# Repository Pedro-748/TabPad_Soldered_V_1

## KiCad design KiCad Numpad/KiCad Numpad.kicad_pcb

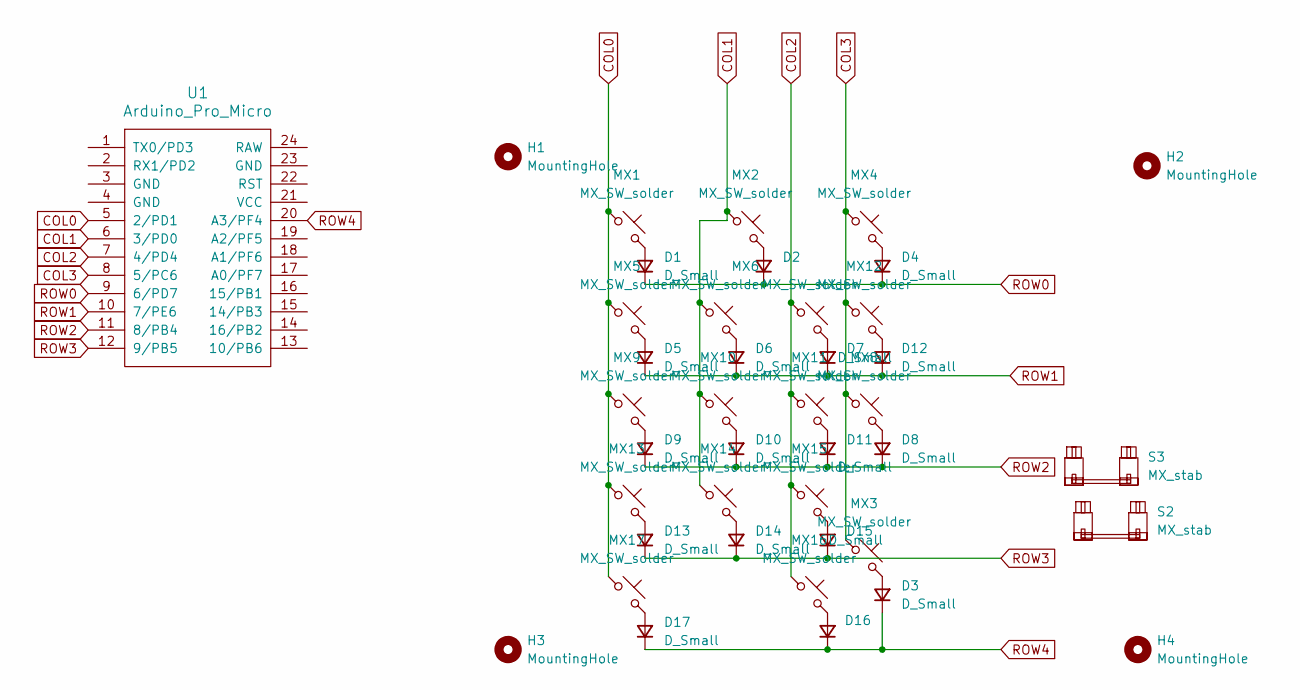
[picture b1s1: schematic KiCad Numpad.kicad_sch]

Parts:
D1, D2, D3, D4, D5, D6, D7, D8, D9, D10, D11, D12, D13, D14, D15, D16, D17: D_Small; D_SOD-123
H1, H2, H3, H4: MountingHole; MountingHole_2.2mm_M2
MX1, MX3, MX5, MX6, MX7, MX8, MX9, MX10, MX11, MX12, MX13, MX14, MX15, MX16, MX17: MX_SW_solder; SW_MX_1u
MX2, MX4: MX_SW_solder; SW_MX_1.5u
S2, S3: MX_stab; STAB_MX_2u
U1: Arduino_Pro_Micro

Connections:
COL0: MX1.1, MX5.1, MX9.1, MX13.1, MX17.1, U1.5 (2/PD1)
COL1: MX2.1, MX6.1, MX10.1, MX14.1, U1.6 (3/PD0)
COL2: MX7.1, MX11.1, MX15.1, MX16.1, U1.7 (4/PD4)
COL3: MX3.1, MX4.1, MX8.1, MX12.1, U1.8 (5/PC6)
unnamed: D1.2 (A), MX1.2
unnamed: D2.2 (A), MX2.2
unnamed: D3.2 (A), MX3.2
unnamed: D4.2 (A), MX4.2
unnamed: D5.2 (A), MX5.2
unnamed: D6.2 (A), MX6.2
unnamed: D7.2 (A), MX7.2
unnamed: D8.2 (A), MX8.2
unnamed: D9.2 (A), MX9.2
unnamed: D10.2 (A), MX10.2
unnamed: D11.2 (A), MX11.2
unnamed: D12.2 (A), MX12.2
unnamed: D13.2 (A), MX13.2
unnamed: D14.2 (A), MX14.2
unnamed: D15.2 (A), MX15.2
unnamed: D16.2 (A), MX16.2
unnamed: D17.2 (A), MX17.2
ROW0: D1.1 (K), D2.1 (K), D4.1 (K), U1.9 (6/PD7)
ROW1: D5.1 (K), D6.1 (K), D7.1 (K), D12.1 (K), U1.10 (7/PE6)
ROW2: D8.1 (K), D9.1 (K), D10.1 (K), D11.1 (K), U1.11 (8/PB4)
ROW3: D13.1 (K), D14.1 (K), D15.1 (K), U1.12 (9/PB5)
ROW4: D3.1 (K), D16.1 (K), D17.1 (K), U1.20 (A3/PF4)

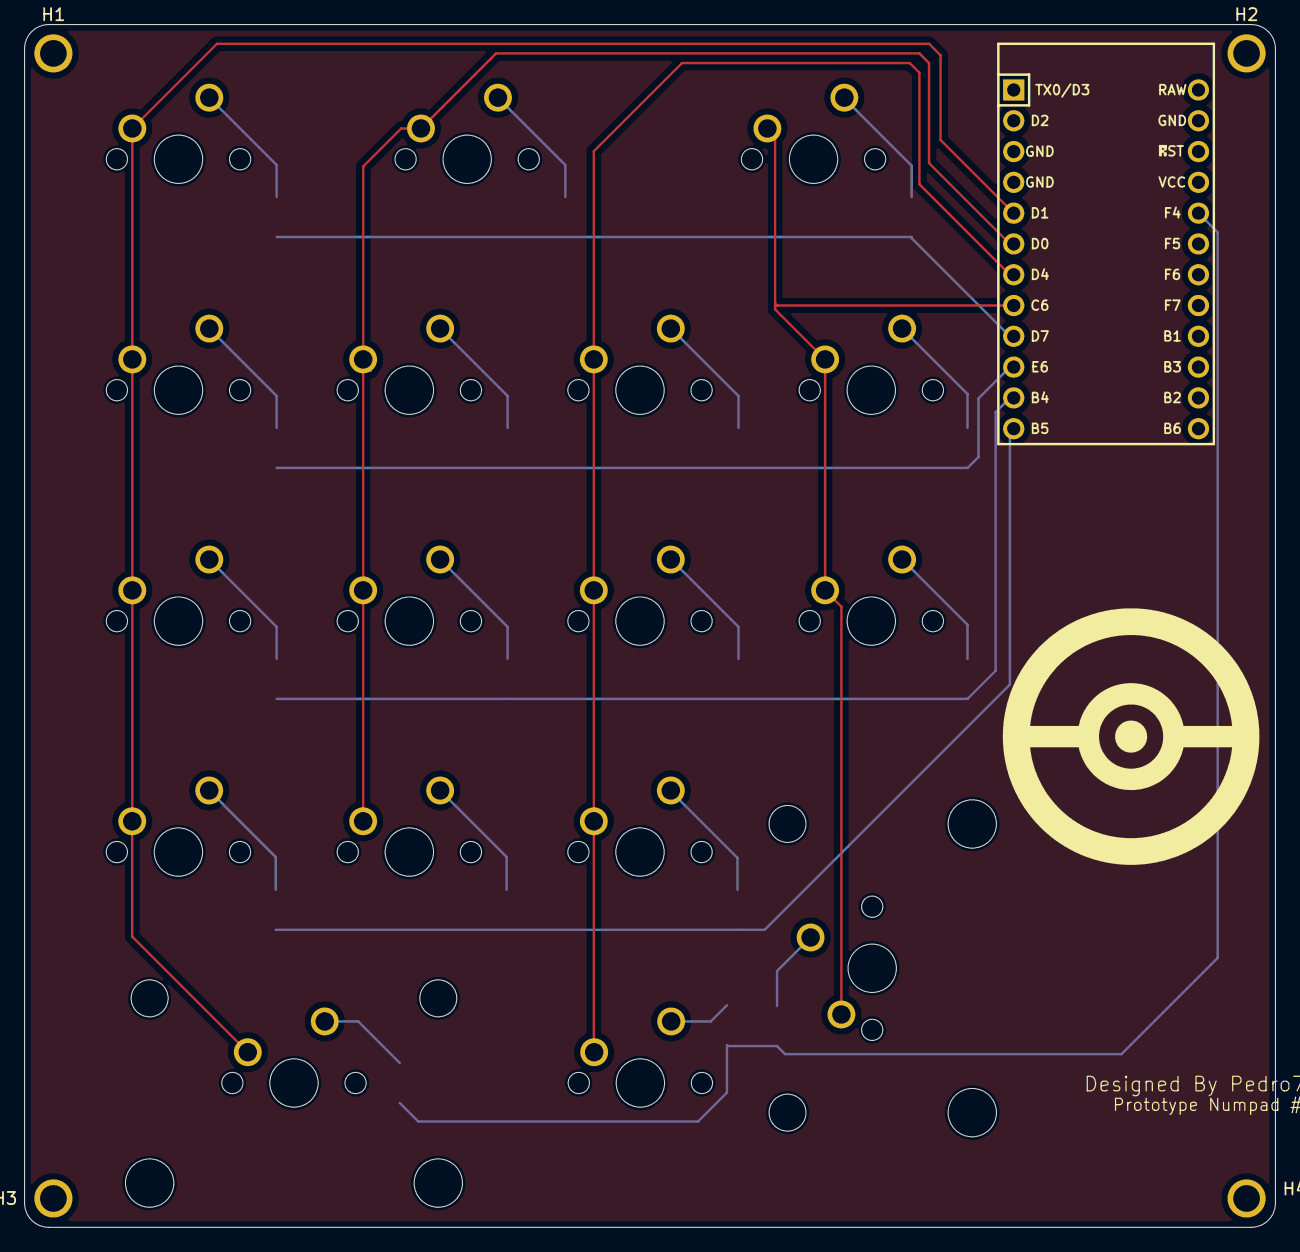
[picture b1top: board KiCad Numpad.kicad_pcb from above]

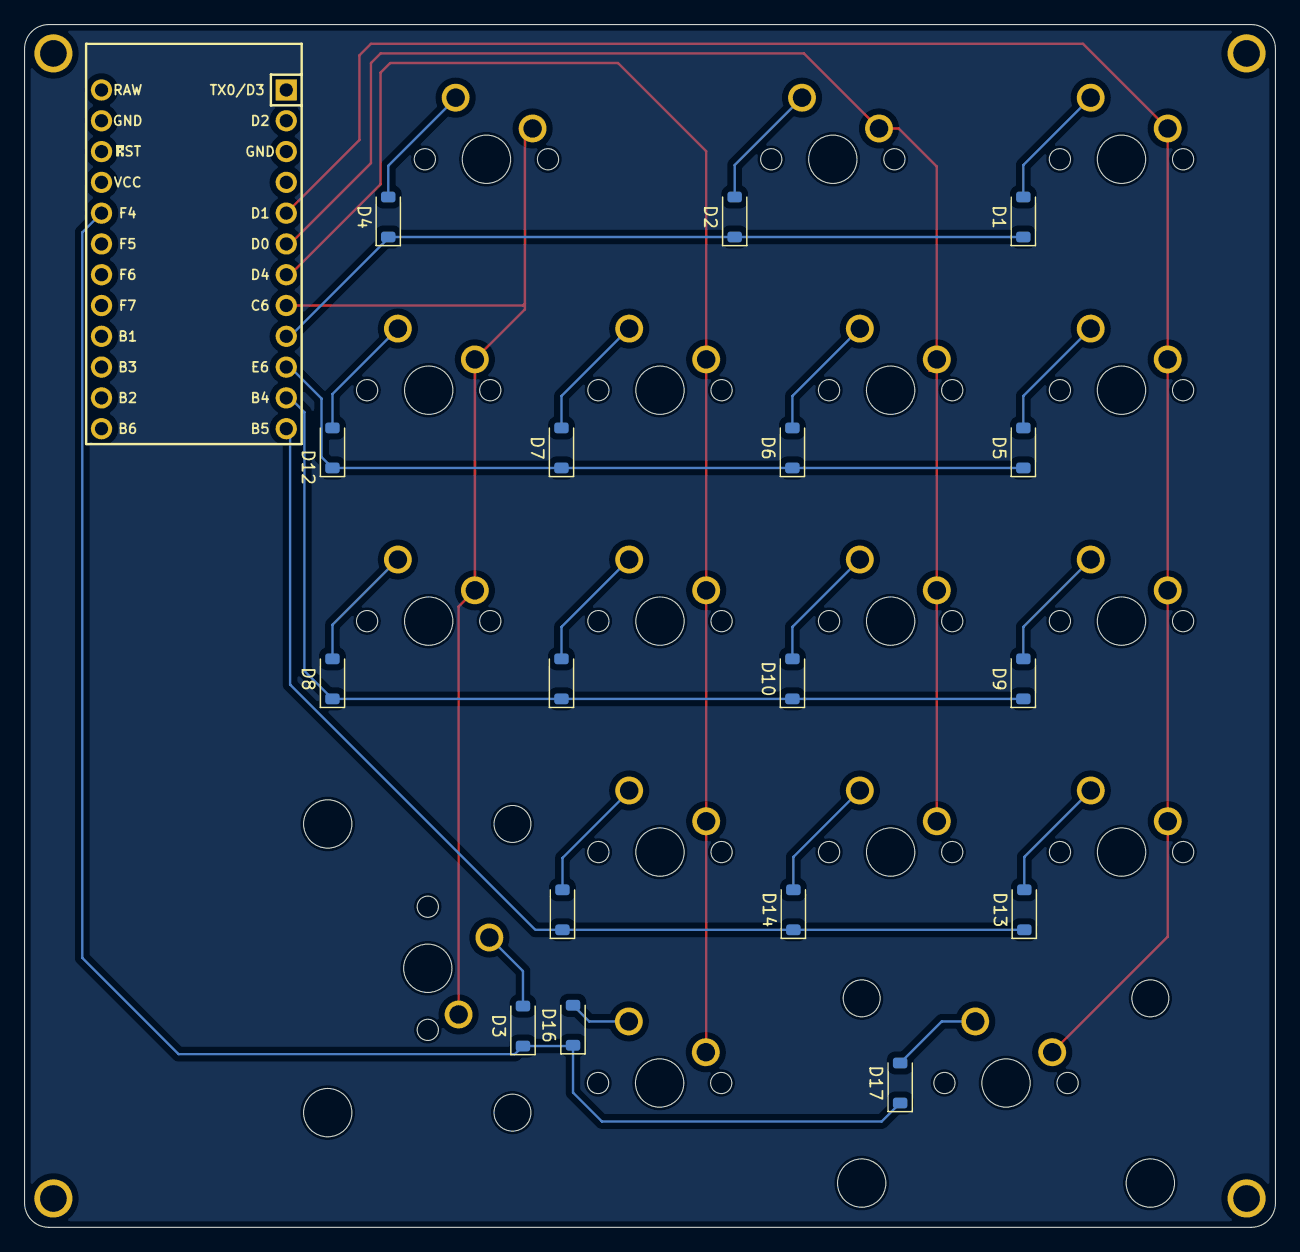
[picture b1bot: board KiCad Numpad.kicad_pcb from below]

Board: 2 copper layers, 103.2 x 99.2 mm, 41 parts (17 on the bottom side), 26 nets.

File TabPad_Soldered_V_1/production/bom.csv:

Designator,Footprint,Quantity,Value,LCSC Part #
"D1, D10, D11, D12, D13, D14, D15, D16, D17, D2, D3, D4, D5, D6, D7, D8, D9",D_SOD-123,17,D_Small,
"MX1, MX10, MX11, MX12, MX13, MX14, MX15, MX16, MX17, MX3, MX5, MX6, MX7, MX8, MX9",SW_MX_1u,15,MX_SW_solder,
"MX2, MX4",SW_MX_1.5u,2,MX_SW_solder,
"S2, S3",STAB_MX_2u,2,MX_stab,
U1,Arduino_Pro_Micro,1,Arduino_Pro_Micro,

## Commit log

2024-05-29 Add File
    add general schematic layout
2024-05-29 misc files
2024-05-29 del files
2024-05-30 push2
2024-05-31 PCB Layout Complete
2024-06-01 Placing Order #1
2024-06-01 push
2024-06-05 hotswap update
2024-07-19 delete
2024-07-19 rename
2024-07-19 Firmware
